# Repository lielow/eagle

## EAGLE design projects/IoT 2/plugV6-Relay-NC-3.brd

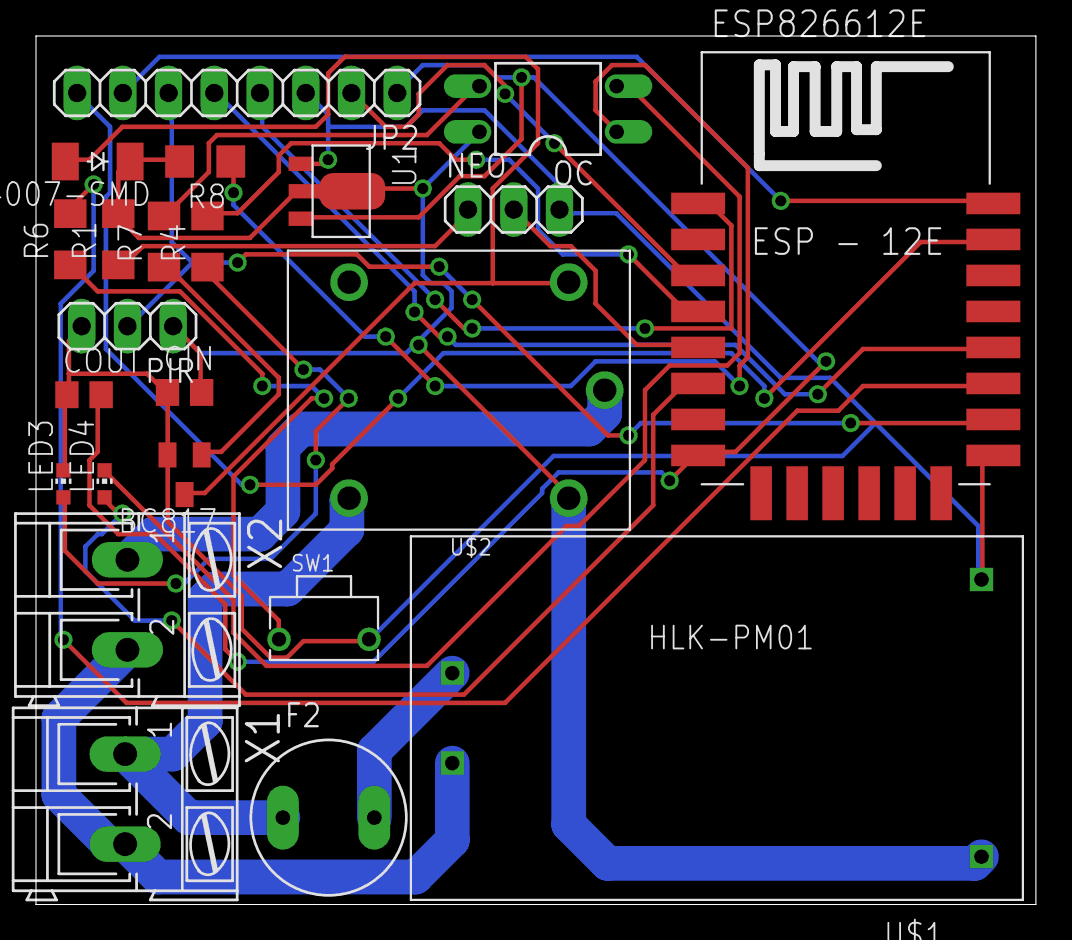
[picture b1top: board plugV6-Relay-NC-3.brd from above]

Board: 2 copper layers, 55.5 x 48.2 mm, 23 parts (0 on the bottom side), 25 nets.

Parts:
1N4007-SMD: CGRM4007-G; SOD-123_MINI-SMA
BC817: SOT23; SOT23-BEC
CIN: 1uF; C0805
COUT: 1uF; C0805
ESP826612E: Value; ESP12E-SMD
F2: TR5
JP2: Interface PIN; 1X08
LED3: 0805; CHIP-LED0603
LED4: 0805-relay; CHIP-LED0603
NEO: 1X03
OC: PC817; DIL04
PIR: 1X03
R1, R4: 230; R1206
R6, R7: 470; R1206
R8: 1K; R1206
SW1: SW2-5.0-6.0X3.0X4.3MM
U1: XC6206PR; SOT89
U$1: HLK-PM01
U$2: RELAY-SONGLE
X1: 220V; AK300/2
X2: Plug; AK300/2

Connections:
+5V: 1N4007-SMD.C, CIN.2, OC.4, PIR.1, R1.2, R8.2, U1.2, U1.4, U$1.+5V, U$2.V+
EN: ESP826612E.CH_PD, JP2.2
GND: BC817.E, CIN.1, COUT.1, ESP826612E.GND, JP2.3, LED3.C, NEO.3, PIR.3, SW1.2, U1.1, U$1.GND
GPIO0: ESP826612E.GPIO0, JP2.5
GPIO2: ESP826612E.GPIO2, R6.2
GPIO12: ESP826612E.GPIO12, LED4.A
GPIO14: ESP826612E.GPIO14, NEO.2
GPIO15: ESP826612E.GPIO15, JP2.6, PIR.2
GPIO16: ESP826612E.GPIO16, R4.2
unnamed: F2.1, U$2.NC, X1.1
unnamed: F2.2, U$1.AC1
unnamed: U$1.AC2, X1.2, X2.2
unnamed: U$2.COM, X2.1
unnamed: OC.3, R7.2
unnamed: BC817.B, R7.1
unnamed: R6.1, SW1.1
unnamed: LED3.A, R4.1
unnamed: NEO.1, R1.1
unnamed: OC.1, R8.1
unnamed: LED4.C, OC.2
unnamed: 1N4007-SMD.A, BC817.C, U$2.V-
RST: ESP826612E.RESET, JP2.4
RX: ESP826612E.RXD0, JP2.8
TX: ESP826612E.TXD0, JP2.7
V33: COUT.2, ESP826612E.VCC, JP2.1, U1.3

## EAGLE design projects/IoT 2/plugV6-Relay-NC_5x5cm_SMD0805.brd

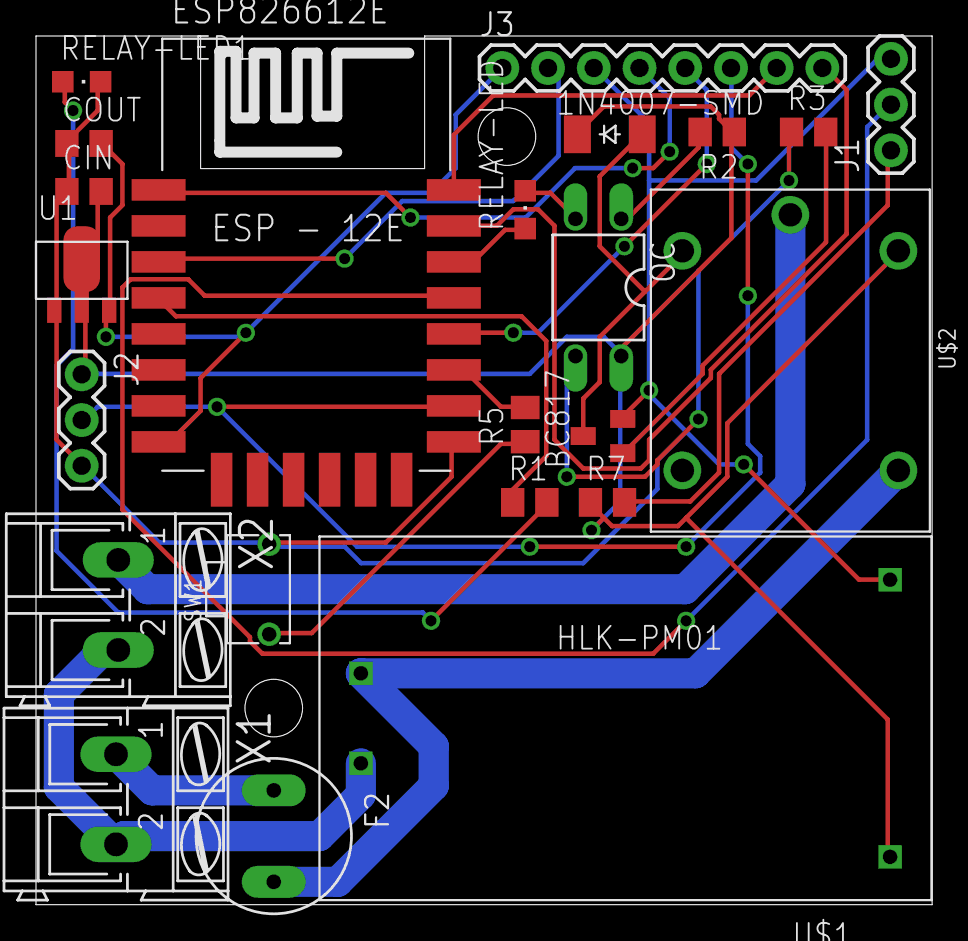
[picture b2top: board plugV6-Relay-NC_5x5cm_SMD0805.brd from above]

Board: 2 copper layers, 49.8 x 48.3 mm, 23 parts (0 on the bottom side), 25 nets.

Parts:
1N4007-SMD: CGRM4007-G; SOD-123_MINI-SMA
BC817: SOT23; SOT23-BEC
CIN: 1uF; C0805
COUT: 1uF; C0805
ESP826612E: Value; ESP12E-SMD
F2: TR5
J1, J2: 1X03
J3: 1X08_ROUND
OC: PC817; DIL04
R1, R7: 230; M0805
R2: 1k; M0805
R3, R5: 470; M0805
RELAY-LED: CHIPLED_0805
RELAY-LED1: ESP-LED; CHIPLED_0805
SW1: SW2-5.0-6.0X3.0X4.3MM
U1: XC6206PR; SOT89
U$1: HLK-PM01
U$2: RELAY-SONGLE
X1: 220V; AK300/2
X2: Plug; AK300/2

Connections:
+5V: 1N4007-SMD.C, CIN.2, J2.1, OC.4, R2.1, R7.1, U1.2, U1.4, U$1.+5V, U$2.V+
EN: ESP826612E.CH_PD, J3.2
GND: BC817.E, CIN.1, COUT.1, ESP826612E.GND, J1.3, J2.3, J3.3, RELAY-LED1.C, SW1.2, U1.1, U$1.GND
GPIO0: ESP826612E.GPIO0, J3.5
GPIO2: ESP826612E.GPIO2, R5.2
GPIO4: ESP826612E.GPIO4, J1.2
GPIO5: ESP826612E.GPIO5, RELAY-LED.A
GPIO15: ESP826612E.GPIO15, J2.2, J3.6
GPIO16: ESP826612E.GPIO16, R1.1
unnamed: F2.2, U$1.AC1, U$2.NC
unnamed: OC.3, R3.1
unnamed: U$1.AC2, X1.2, X2.2
unnamed: U$2.COM, X2.1
unnamed: BC817.B, R3.2
unnamed: OC.2, RELAY-LED.C
unnamed: R5.1, SW1.1
unnamed: R1.2, RELAY-LED1.A
unnamed: J1.1, R7.2
unnamed: F2.1, X1.1
unnamed: OC.1, R2.2
unnamed: 1N4007-SMD.A, BC817.C, U$2.V-
RST: ESP826612E.RESET, J3.4
RX: ESP826612E.RXD0, J3.8
TX: ESP826612E.TXD0, J3.7
V33: COUT.2, ESP826612E.VCC, J3.1, U1.3

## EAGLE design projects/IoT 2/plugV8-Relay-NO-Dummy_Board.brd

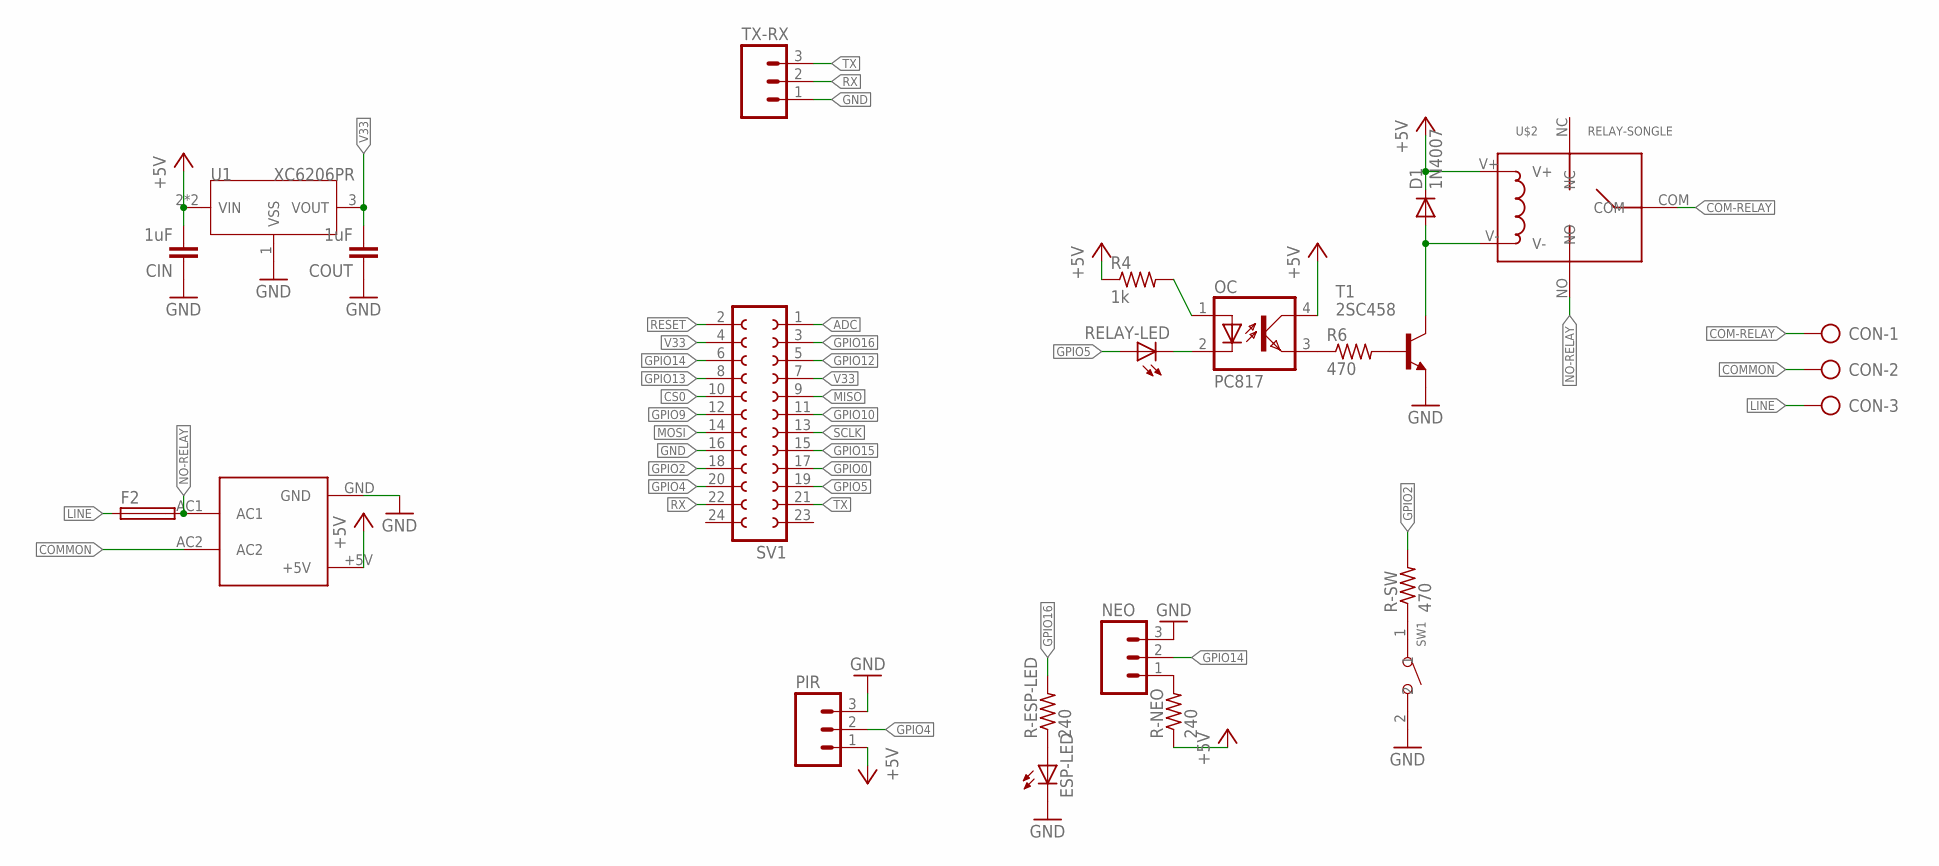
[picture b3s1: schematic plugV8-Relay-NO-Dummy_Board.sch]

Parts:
CIN: 1uF; C0805
CON: AK300/3
COUT: 1uF; C0805
D1: 1N4007; DO41-10
ESP-LED: LED3MM
F2: TR5
NEO: M03PTH; 1X03
OC: PC817; DIL04
PIR: M03PTH; 1X03
R4: 1k; 0204/7
R6: 470; 0204/7
R-ESP-LED: 240; 0204/7
R-NEO: 240; 0204/7
R-SW: 470; 0204/7
RELAY-LED: LED3MM
SV1: FE12-2
SW1: DIP-BUTTON(2P-6.0X3.0X4.3MM)-TS-1101F; SW2-5.0-6.0X3.0X4.3MM
T1: 2SC458; TO92-ECB
TX-RX: M03PTH; 1X03
U1: XC6206PR; SOT89
U$1: HLK-PM01
U$2: RELAY-SONGLE

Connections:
+5V: CIN.2, D1.C, OC.4 (COL), PIR.1, R4.1, R-NEO.1, U1.2 (VIN), U1.4 (VIN), U$1.+5V, U$2.V+
ADC: SV1.1
COM-RELAY: CON.1, U$2.COM
COMMON: CON.2, U$1.AC2
CS0: SV1.10
GND: CIN.1, COUT.1, ESP-LED.K (C), NEO.3, PIR.3, SV1.16, SW1.2, T1.E, TX-RX.1, U1.1 (VSS), U$1.GND
GPIO0: SV1.17
GPIO2: R-SW.2, SV1.18
GPIO4: PIR.2, SV1.20
GPIO5: RELAY-LED.A, SV1.19
GPIO9: SV1.12
GPIO10: SV1.11
GPIO12: SV1.5
GPIO13: SV1.8
GPIO14: NEO.2, SV1.6
GPIO15: SV1.15
GPIO16: R-ESP-LED.2, SV1.3
LINE: CON.3, F2.1
MISO: SV1.9
MOSI: SV1.14
unnamed: ESP-LED.A, R-ESP-LED.1
unnamed: OC.3 (EMIT), R6.1
unnamed: R6.2, T1.B
unnamed: NEO.1, R-NEO.2
unnamed: R-SW.1, SW1.1
unnamed: OC.2 (C), RELAY-LED.K (C)
unnamed: OC.1 (A), R4.2
unnamed: D1.A, T1.C, U$2.V-
NO-RELAY: F2.2, U$1.AC1, U$2.NO
RESET: SV1.2
RX: SV1.22, TX-RX.2
SCLK: SV1.13
TX: SV1.21, TX-RX.3
V33: COUT.2, SV1.4, SV1.7, U1.3 (VOUT)

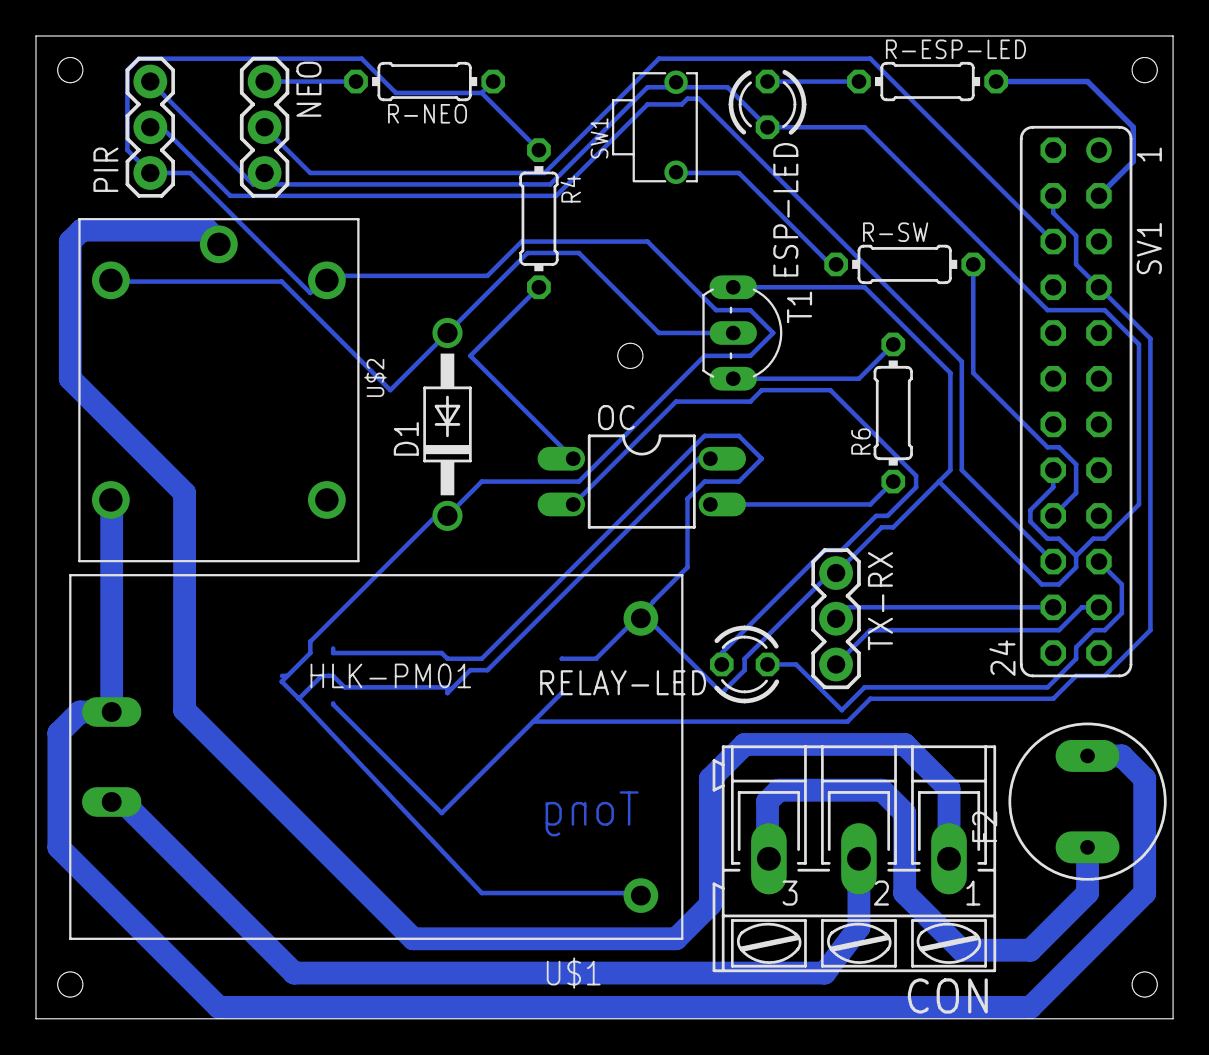
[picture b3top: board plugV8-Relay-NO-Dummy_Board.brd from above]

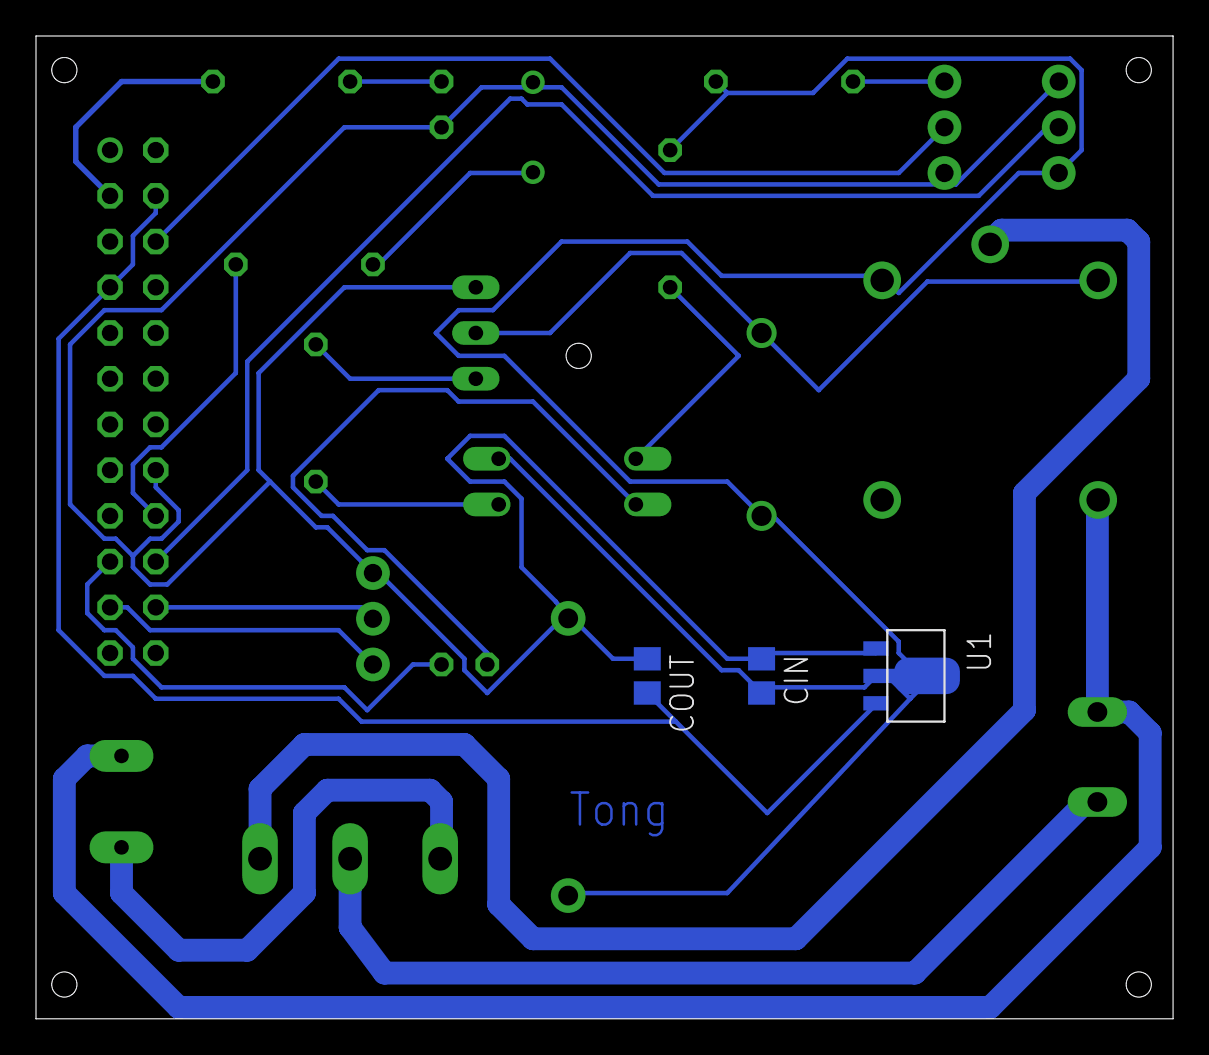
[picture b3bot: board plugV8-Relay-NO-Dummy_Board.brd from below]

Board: 2 copper layers, 63.2 x 54.6 mm, 22 parts (3 on the bottom side), 22 nets.

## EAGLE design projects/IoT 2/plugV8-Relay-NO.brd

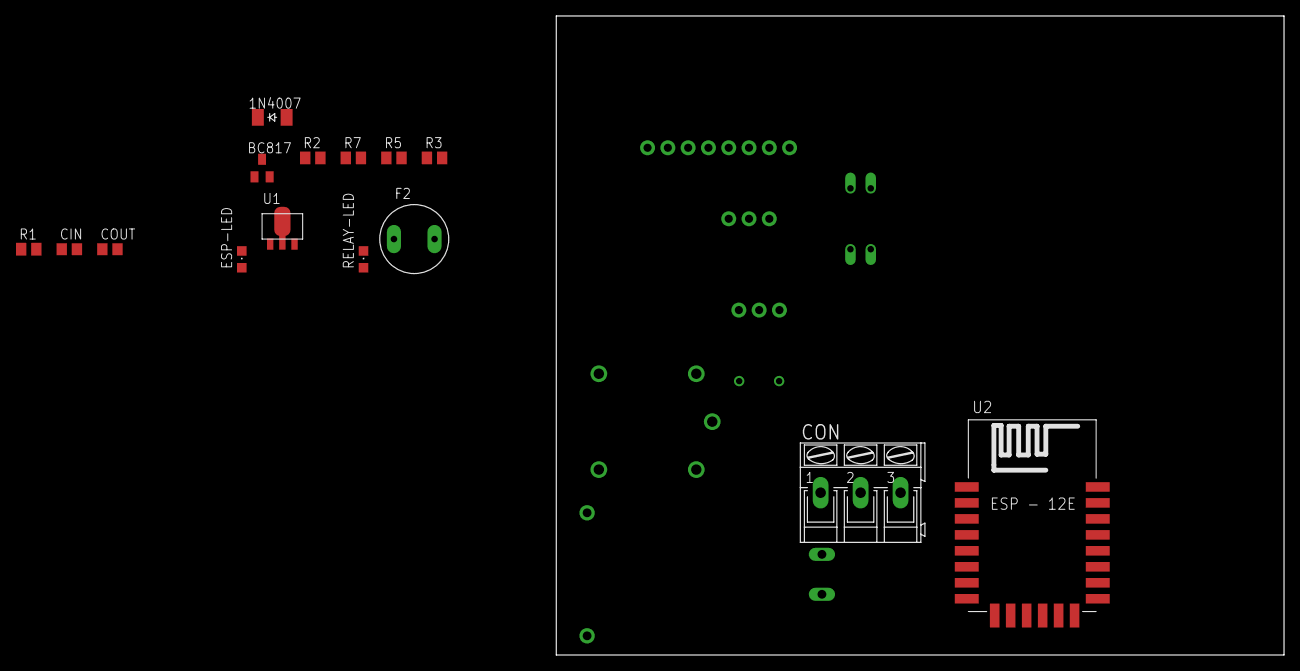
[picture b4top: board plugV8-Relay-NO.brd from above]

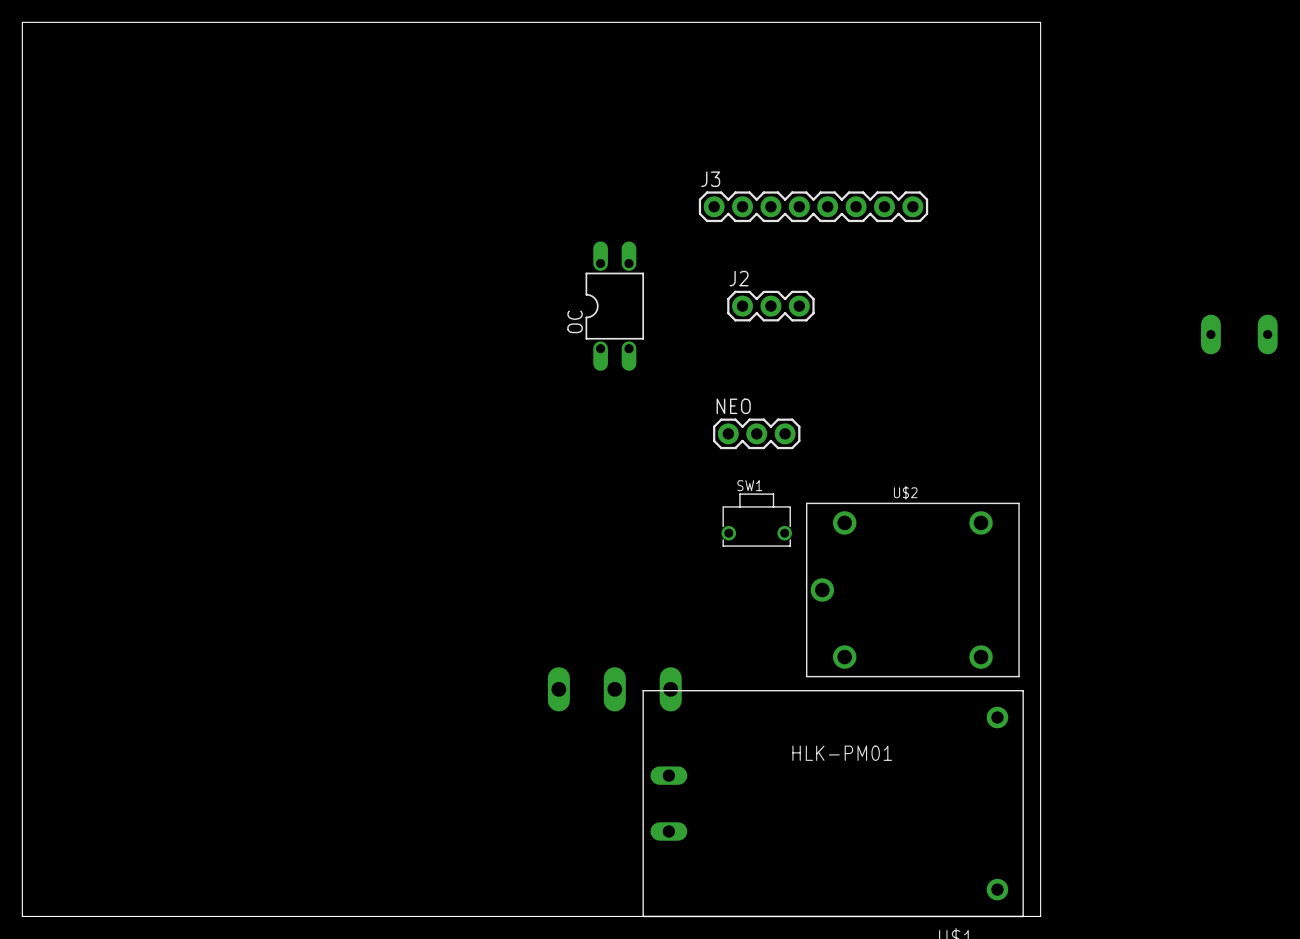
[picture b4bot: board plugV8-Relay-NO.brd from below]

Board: 2 copper layers, 91.1 x 80.0 mm, 22 parts (7 on the bottom side), 24 nets, no tracks yet.

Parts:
1N4007: SOD-123_MINI-SMA
BC817: SOT23-BEC
CIN: 1uF; C0805
CON: AK300/3
COUT: 1uF; C0805
ESP-LED: CHIPLED_0805
F2: TR5
J2: 1X03
J3: 1X08_ROUND
NEO: 1X03
OC: PC817; DIL04
R1, R7: 240; M0805
R2: 1k; M0805
R3, R5: 470; M0805
RELAY-LED: CHIPLED_0805
SW1: SW2-5.0-6.0X3.0X4.3MM
U1: XC6206PR; SOT89
U2: ESP12E-SMD
U$1: HLK-PM01
U$2: RELAY-SONGLE

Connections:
+5V: 1N4007.C, CIN.2, J2.1, OC.4, R2.1, R7.1, U1.2, U1.4, U$1.+5V, U$2.V+
GND: BC817.E, CIN.1, COUT.1, ESP-LED.C, J2.3, J3.3, NEO.3, SW1.2, U1.1, U2.GND, U2.GPIO15, U$1.GND
GPIO0: J3.5, U2.GPIO0
GPIO2: R5.2, U2.GPIO2
GPIO4: J2.2, U2.GPIO4
GPIO5: RELAY-LED.A, U2.GPIO5
GPIO14: NEO.2, U2.GPIO14
GPIO16: R1.1, U2.GPIO16
unnamed: F2.2, U$1.AC1, U$2.NO
unnamed: OC.3, R3.1
unnamed: CON.2, U$1.AC2
unnamed: CON.1, U$2.COM
unnamed: BC817.B, R3.2
unnamed: OC.2, RELAY-LED.C
unnamed: R5.1, SW1.1
unnamed: ESP-LED.A, R1.2
unnamed: NEO.1, R7.2
unnamed: CON.3, F2.1
unnamed: OC.1, R2.2
unnamed: 1N4007.A, BC817.C, U$2.V-
RST: J3.4, U2.RESET
RX: J3.8, U2.RXD0
TX: J3.7, U2.TXD0
V33: COUT.2, J3.1, U1.3, U2.CH_PD, U2.VCC

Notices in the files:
parts and their libraries:
SparkFun-Connectors: Licensing: Creative Commons ShareAlike 4.0 International - https://creativecommons.org/licenses/by-sa/4.0
